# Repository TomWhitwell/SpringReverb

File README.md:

# Music Thing Spring Reverb  

This repository contains PCB files for the Music Thing Spring Reverb project.  

Full documentation at [Music Thing Modular](http://musicthing.co.uk/modular/?page_id=579)  

Please [report any issues in the Issue Log](https://github.com/TomWhitwell/SpringReverb/issues)

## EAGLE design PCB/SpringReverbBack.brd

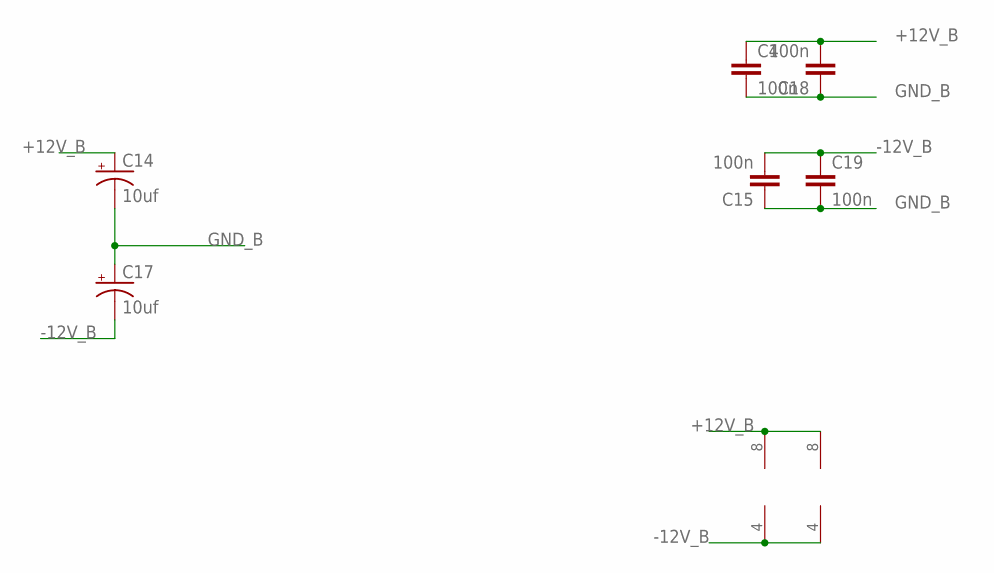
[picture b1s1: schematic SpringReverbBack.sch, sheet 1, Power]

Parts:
BRICK: TL072; DIL08
C4, C15, C18, C19: 100n; C050-024X044
C14, C17: 10uf; CPOL-RADIAL-10UF-25V
IC4_DRV_RCVR: TL072; DIL08

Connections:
+12V_B: BRICK.8 (V+), C4.1, C14.1 (+), C18.2, IC4_DRV_RCVR.8 (V+); also elsewhere on the board
-12V_B: BRICK.4 (V-), C15.2, C17.2 (-), C19.1, IC4_DRV_RCVR.4 (V-); also elsewhere on the board
GND_B: C4.2, C14.2 (-), C15.1, C17.1 (+), C18.1, C19.2; also elsewhere on the board

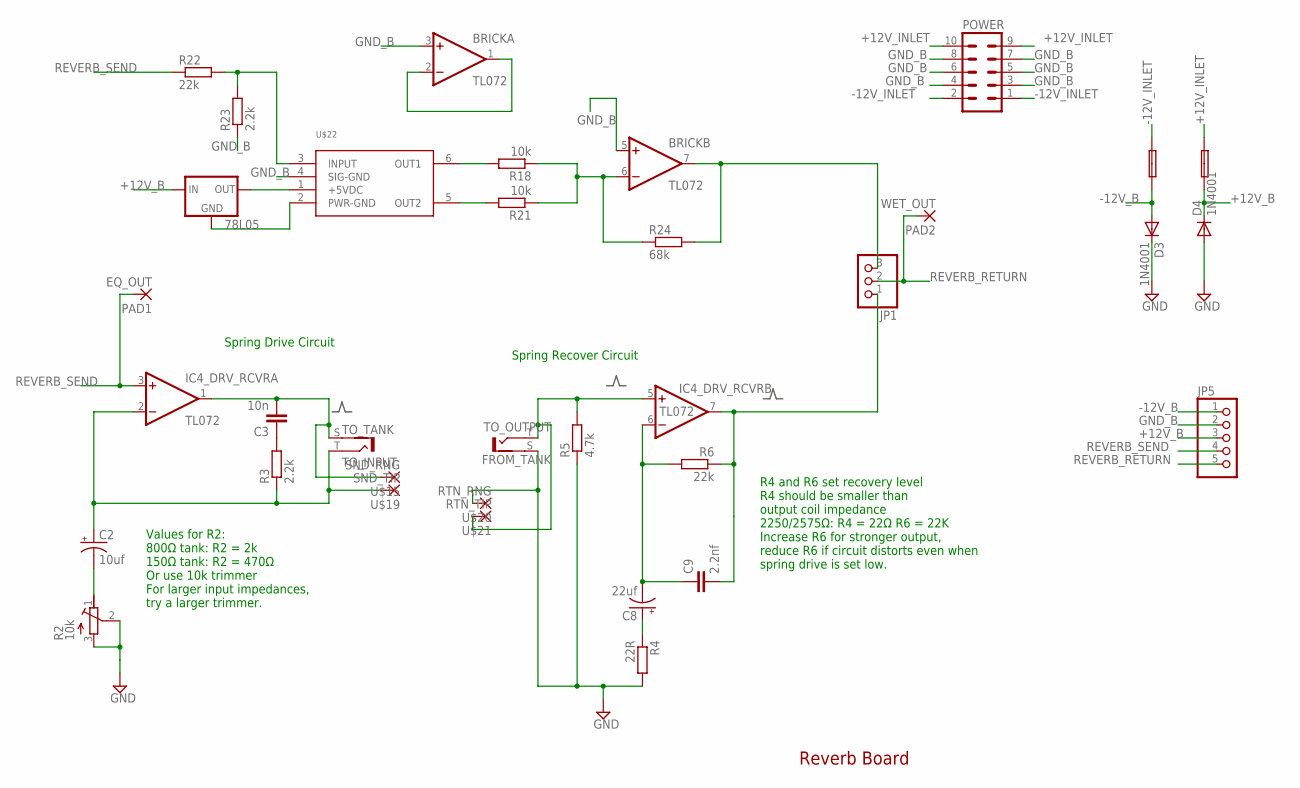
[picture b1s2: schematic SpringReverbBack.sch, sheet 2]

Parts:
0.1A_FUSE, 0.1A_FUSE_2: FUSE; C050H075X075
78L05: V_REG_78XXTO-92; TO-92
BRICK: TL072; DIL08
C2: 10uf; CPOL-RADIAL-10UF-25V
C3: 10n; C050-024X044
C8: 22uf; CPOL-RADIAL-10UF-25V
C9: 2.2nf; C050-024X044
D3, D4: 1N4001; DO41-10
IC4_DRV_RCVR: TL072; DIL08
JP1: PINHD-1X3; 1X03
JP5: PINHD-1X5; 1X05
PAD1: EQ_OUT; LONG_PAD_1
PAD2: WET_OUT; LONG_PAD_1
POWER: 10_PIN_HEADER; MA05-2
R2: 10k; RTRIMT93YA
R3, R23: 2.2k; 0207/10
R4: 22R; 0207/10
R5: 4.7k; 0207/10
R6, R22: 22k; 0207/10
R18, R21: 10k; 0207/10
R24: 68k; 0207/10
TO_INPUT: TO_TANK; BTOR1
TO_OUTPUT: FROM_TANK; BTOR1
U$15: SND_RNG; LONG_PAD_1
U$19: SND_TIP; LONG_PAD_1
U$20: RTN_RNG; LONG_PAD_1
U$21: RTN_TIP; LONG_PAD_1
U$22: BTDR-2H

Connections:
+12V_B: 0.1A_FUSE_2.1, 78L05.3 (IN), D4.C, JP5.3; also elsewhere on the board
+12V_INLET: 0.1A_FUSE_2.2, POWER.9, POWER.10
-12V_B: 0.1A_FUSE.1, D3.A, JP5.1; also elsewhere on the board
-12V_INLET: 0.1A_FUSE.2, POWER.1, POWER.2
GND_B: BRICK.3 (+IN), BRICK.5 (+IN), D3.C, D4.A, JP5.2, POWER.3, POWER.4, POWER.5, POWER.6, POWER.7, POWER.8, R2.2 (S), R2.3 (E), R4.2, R5.1, R23.1, TO_OUTPUT.S (2), U$20.P$1, U$22.4 (SIG-GND); also elsewhere on the board
unnamed: C2.2 (-), R2.1 (A)
unnamed: C3.1, R3.2
unnamed: C3.2, IC4_DRV_RCVR.1 (OUT), TO_INPUT.S (2), U$15.P$1
unnamed: C2.1 (+), IC4_DRV_RCVR.2 (-IN), R3.1, TO_INPUT.T (1), U$19.P$1
unnamed: IC4_DRV_RCVR.5 (+IN), R5.2, TO_OUTPUT.T (1), U$21.P$1
unnamed: C8.1 (+), R4.1
unnamed: C8.2 (-), C9.1, IC4_DRV_RCVR.6 (-IN), R6.2
unnamed: 78L05.1 (OUT), U$22.1 (+5VDC)
unnamed: R22.2, R23.2, U$22.3 (INPUT)
unnamed: R18.2, U$22.6 (OUT1)
unnamed: R21.2, U$22.5 (OUT2)
unnamed: BRICK.6 (-IN), R18.1, R21.1, R24.1
unnamed: 78L05.2 (GND), U$22.2 (PWR-GND)
unnamed: BRICK.1 (OUT), BRICK.2 (-IN)
unnamed: BRICK.7 (OUT), JP1.3, R24.2
unnamed: C9.2, IC4_DRV_RCVR.7 (OUT), JP1.1, R6.1
REVERB_RETURN: JP1.2, JP5.5, PAD2.P$1
REVERB_SEND: IC4_DRV_RCVR.3 (+IN), JP5.4, PAD1.P$1, R22.1

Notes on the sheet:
Values for R2: 800Ω tank: R2 = 2k 150Ω tank: R2 = 470Ω Or use 10k trimmer For larger input impedances, try a larger trimmer.
Spring Drive Circuit
R4 and R6 set recovery level R4 should be smaller than output coil impedance 2250/2575Ω: R4 = 22Ω R6 = 22K Increase R6 for stronger output, reduce R6 if circuit distorts even when spring drive is set low.
Spring Recover Circuit
Reverb Board

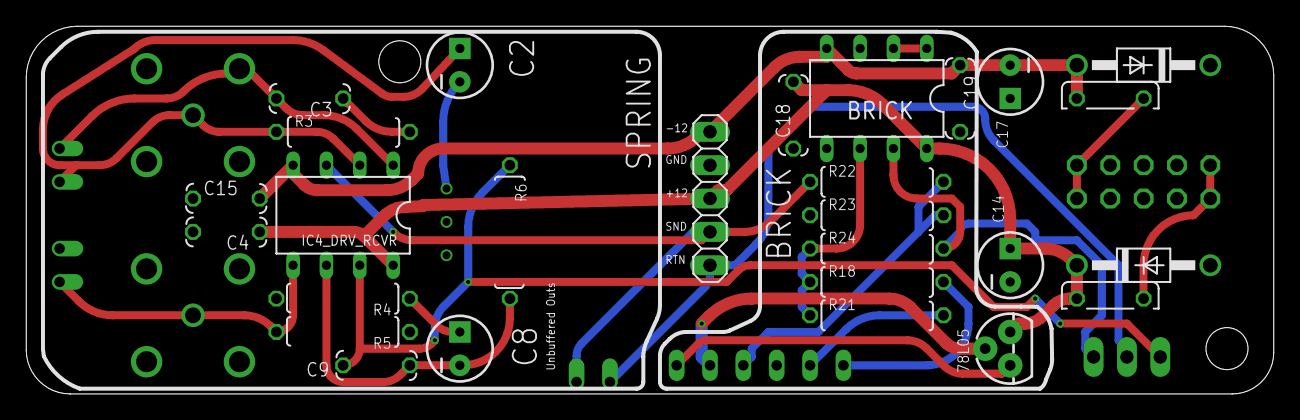
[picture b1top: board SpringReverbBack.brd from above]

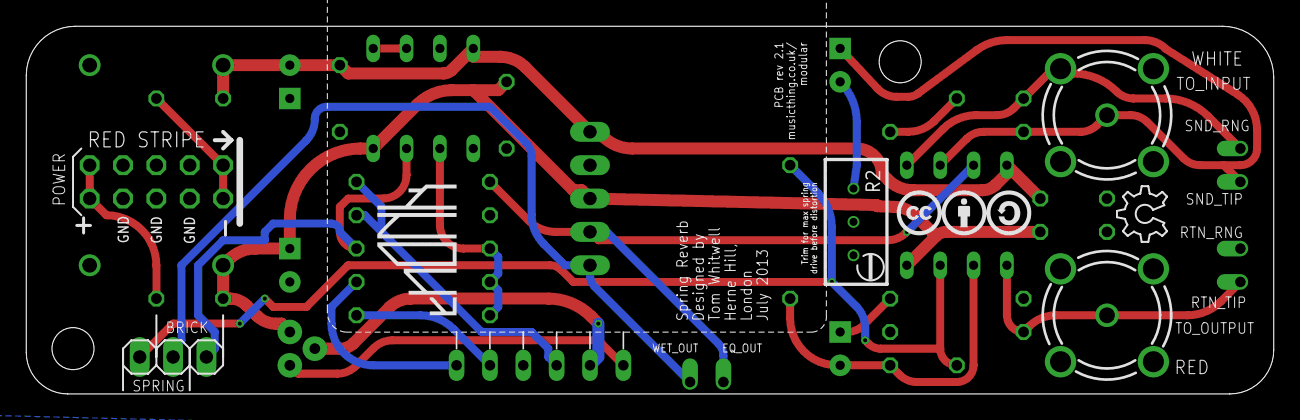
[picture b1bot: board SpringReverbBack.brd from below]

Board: 4 copper layers, 95.0 x 28.0 mm, 43 parts (10 on the bottom side), 23 nets.

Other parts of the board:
U$1: CC_1CM_SCREENPRINT
U$2: MTM_1CM_KEEPOUT
U$3: OSHW_6X150_NOTEXT
U$4: THONK_1CM_SCREENPRINT

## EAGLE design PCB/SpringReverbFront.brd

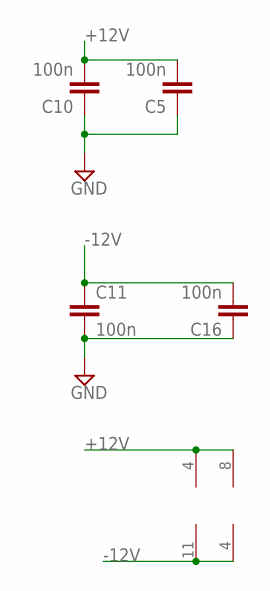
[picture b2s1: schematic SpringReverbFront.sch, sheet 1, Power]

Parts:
C5, C10, C11, C16: 100n; C050-024X044
IC1: TL074; DIL14
IC2_EQ: NE5532; DIL08

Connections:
+12V: C5.2, C10.2, IC1.4 (V+), IC2_EQ.8 (V+); also elsewhere on the board
-12V: C11.1, C16.2, IC1.11 (V-), IC2_EQ.4 (V-); also elsewhere on the board
GND: C5.1, C10.1, C11.2, C16.1; also elsewhere on the board

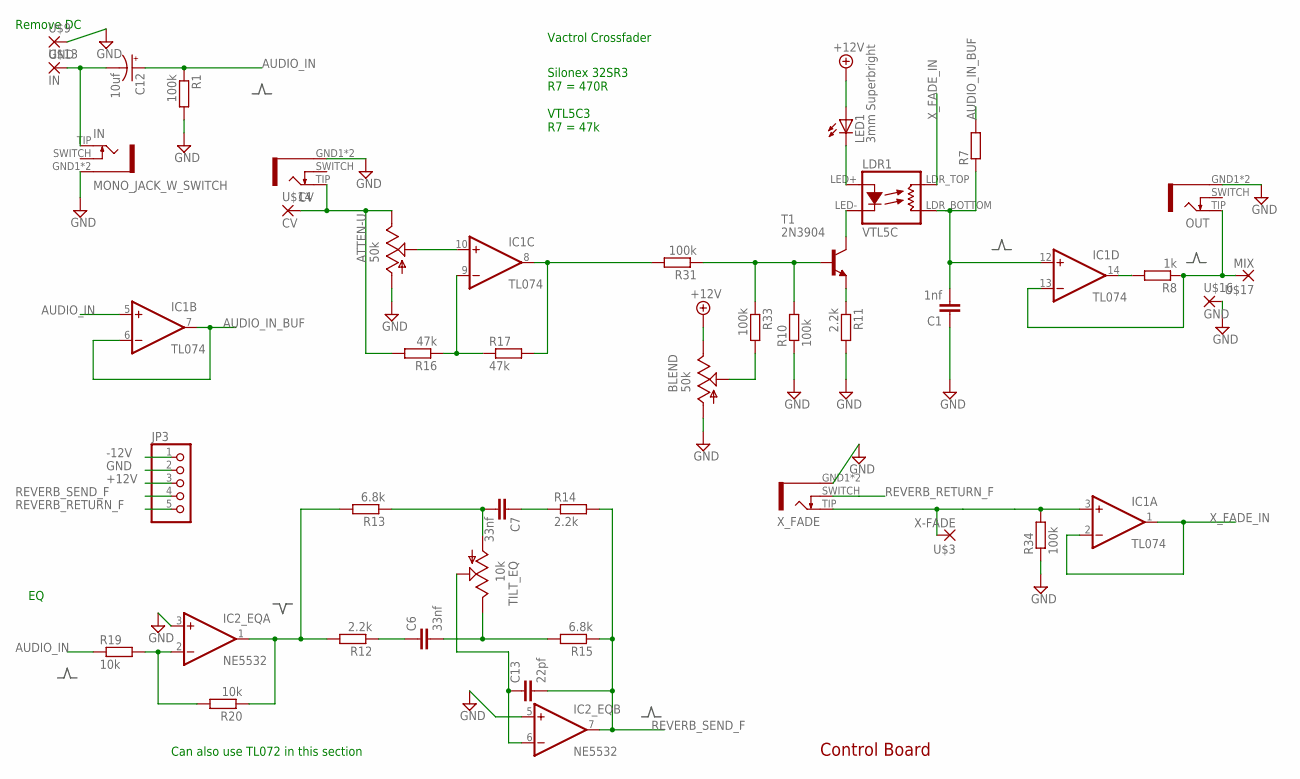
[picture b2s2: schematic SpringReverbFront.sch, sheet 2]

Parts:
ATTEN-U: 50k; EVUF
BLEND: 50k; EVUF
C1: 1nf; C050-024X044
C6, C7: 33nf; C050-024X044
C12: 10uf; 050_020
C13: 22pf; 050X030_025
CV: MONO_JACK_W_SWITCH; ERTHENVAR
IC1: TL074; DIL14
IC2_EQ: NE5532; DIL08
IN: MONO_JACK_W_SWITCH; ERTHENVAR
JP3: PINHD-1X5; 1X05
LDR1: VTL5C; VACTROL_COMPACT
LED1: 3mm Superbright; LED3MM
OUT: MONO_JACK_W_SWITCH; ERTHENVAR
R1: 100k; VERT-RESISTOR
R7: R-EU_STANDARD_RESISTOR; 0207/10
R8: 1k; 0207/10
R10, R31, R33, R34: 100k; 0207/10
R11, R12, R14: 2.2k; 0207/10
R13, R15: 6.8k; 0207/10
R16, R17: 47k; VERT-RESISTOR
R19: 10k; VERT-RESISTOR
R20: 10k; 0207/10
T1: 2N3904; TO92
TILT_EQ: 10k; EVUF
U$3: X-FADE; LONG_PAD_1
U$9, U$16: GND; LONG_PAD_1
U$13: IN; LONG_PAD_1
U$14: CV; LONG_PAD_1
U$17: MIX; LONG_PAD_1
X_FADE: MONO_JACK_W_SWITCH; ERTHENVAR

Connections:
+12V: BLEND.3 (E), JP3.3, LED1.A; also elsewhere on the board
-12V: JP3.1; also elsewhere on the board
AUDIO_IN: C12.+, IC1.5 (+IN), R1.1, R19.1
AUDIO_IN_BUF: IC1.6 (-IN), IC1.7 (OUT), R7.2
GND: ATTEN-U.1 (A), BLEND.1 (A), C1.1, CV.GND1 (SLEEVE), CV.GND2 (SLEEVE), IC2_EQ.3 (+IN), IC2_EQ.5 (+IN), IN.GND1 (SLEEVE), IN.GND2 (SLEEVE), JP3.2, OUT.GND1 (SLEEVE), OUT.GND2 (SLEEVE), R1.2, R10.1, R11.2, R34.1, U$9.P$1, U$16.P$1, X_FADE.GND1 (SLEEVE), X_FADE.GND2 (SLEEVE); also elsewhere on the board
MIX_OUT_B: IC1.13 (-IN), OUT.TIP, R8.1, U$17.P$1
unnamed: C12.-, IN.TIP, U$13.P$1
unnamed: IC1.3 (+IN), R34.2, U$3.P$1, X_FADE.TIP
unnamed: ATTEN-U.3 (E), CV.TIP, R16.2, U$14.P$1
unnamed: C6.1, R12.1
unnamed: BLEND.2 (S), R33.2
unnamed: IC1.14 (OUT), R8.2
unnamed: C6.2, R15.2, TILT_EQ.3 (E)
unnamed: R11.1, T1.3 (E)
unnamed: C7.2, R13.1, TILT_EQ.1 (A)
unnamed: ATTEN-U.2 (S), IC1.10 (+IN)
unnamed: C7.1, R14.1
unnamed: C13.1, IC2_EQ.6 (-IN), TILT_EQ.2 (S)
unnamed: IC1.9 (-IN), R16.1, R17.1
unnamed: IC2_EQ.2 (-IN), R19.2, R20.2
unnamed: IC1.8 (OUT), R17.2, R31.2
unnamed: LDR1.LED+, LED1.K (C)
unnamed: IC2_EQ.1 (OUT), R12.2, R13.2, R20.1
unnamed: R10.2, R31.1, R33.1, T1.2 (B)
unnamed: LDR1.LED-, T1.1 (C)
REVERB_RETURN_F: JP3.5, X_FADE.SWITCH
REVERB_SEND_F: C13.2, IC2_EQ.7 (OUT), JP3.4, R14.2, R15.1
SUM: C1.2, IC1.12 (+IN), LDR1.LDR_BOTTOM (RES2), R7.1
X_FADE_IN: IC1.1 (OUT), IC1.2 (-IN), LDR1.LDR_TOP (RES1)

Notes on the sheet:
Control Board
Vactrol Crossfader
Silonex 32SR3 R7 = 470R VTL5C3 R7 = 47k
Remove DC
Can also use TL072 in this section

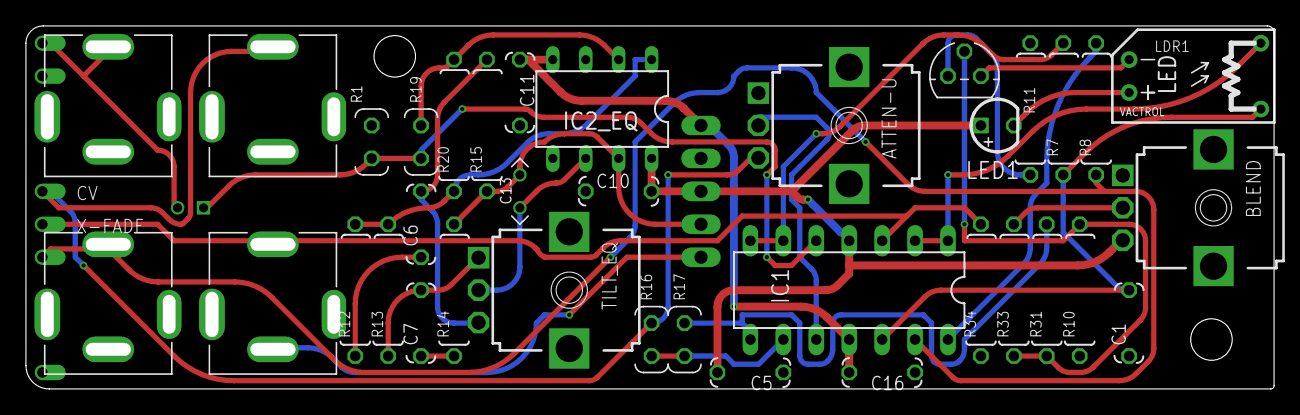
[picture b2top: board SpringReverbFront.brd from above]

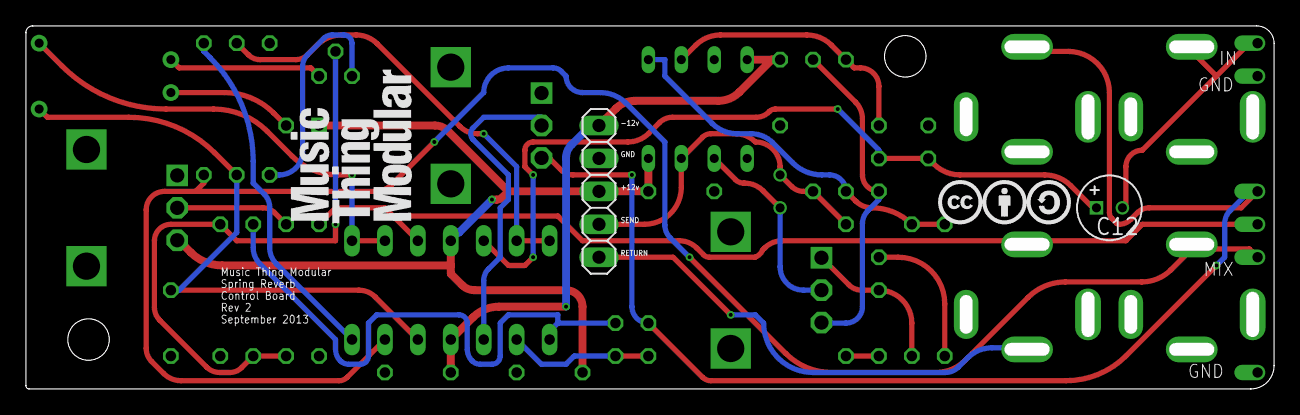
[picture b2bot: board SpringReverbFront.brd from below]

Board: 4 copper layers, 96.3 x 28.0 mm, 46 parts (4 on the bottom side), 29 nets.

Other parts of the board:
U$8: CC_1CM_SCREENPRINT
U$10: MTM_1CM

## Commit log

2015-01-07 Upload files as manufactured rev 2.1
2015-01-07 Updated to Eagle 7.2
2015-01-22 Adding forum backup

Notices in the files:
parts and their libraries:
SparkFun-Passives: Licensing: CC v3.0 Share-Alike You are welcome to use this library for commercial purposes.
